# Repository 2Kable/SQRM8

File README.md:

# SQRM8

SQRM8 (say "Squaremate") is the square mate for your agents: a desk companion for
[Claude Code](https://claude.com/claude-code). A square 4" touch screen on your USB port shows every Claude Code
agent running on your machine: which one is working, which one **needs you**, what each agent and subagent is
doing, and how much of your plan is left. Built for people who run several agents in parallel and want to stop
alt-tabbing to check on them.

Nothing leaves your machine: a small daemon reads Claude Code's local data and talks to the device over the USB
cable. There is no cloud and no account. The only network access is a once-a-day look at this repository's
[Releases page](https://github.com/d-weber/SQRM8/releases) for a newer app version (public release
metadata, nothing about you); turn it off with **Check for updates daily** in the menu.

## What you see

Swipe between screens. Tap a session to open its detail view.

- **Home** is M8's Studio, a pixel-art room. M8, an original character, walks to the station of whatever your
  agents are doing: desk to write code, bookshelf to read, server rack to run commands, whiteboard to plan, bed
  when nothing runs. Subagents show up as little helpers. When a session needs you, M8 stands at the door with a
  big "!". The band below is pixel art too: clock, date and the 5-hour / weekly plan gauges, plus the per-model
  week (FA for Fable).
- **Agents** is one card per session: status, current tool, todo progress, context use, subagents.
- **Detail** shows the selected session's current action, tokens, cost, context, model and todos, with a
  **Focus** button that brings its terminal to the front.
- **Activity** is a live feed of tool calls, prompts, errors and finished turns, filterable to "needs me".
- **Usage** shows your 5-hour and weekly plan limits, today's cost and tokens, the model mix and hourly charts.
- **System** is a btop-style view of CPU, memory, top processes and network.
- **Orbit** draws sessions as planets around M8, subagents as moons.

When a session is blocked on a permission prompt or a question, an amber glow lights the edges of the screen and a
"needs you" card appears over whatever you are looking at. When a session finishes, a small celebration plays.
After a few minutes of inactivity the screen dims, then turns into a night clock.
A device that is powered up and hears nothing from the app shows a QR code to this page; once the app has talked
to it, it keeps its usual screens until the next power-up, even while the computer is off.

M8's pixel art is being redrawn; the screenshots above still show the earlier version.

## Hardware

- A Waveshare [ESP32-S3-Touch-LCD-4B](https://www.waveshare.com/wiki/ESP32-S3-Touch-LCD-4B): a 4" 480×480 IPS
  panel with capacitive touch and an ESP32-S3 behind it. The older ESP32-S3-Touch-LCD-4 (V4) was supported up to
  firmware 0.3.0 and is not any more.
- A USB-C **data** cable (not a charge-only one).

Plug the cable into the board's **USB-OTG** port, not the "USB TO UART" one. The host link runs over the
ESP32-S3's native USB, and the UART port only works for flashing. The app flashes the firmware for you.

## Install

Download the app for your OS from the [Releases page](https://github.com/d-weber/SQRM8/releases). It
bundles the device firmware, so there is nothing else to install. The builds are not code-signed, so each OS warns
once.

| OS | File | Notes |
|---|---|---|
| Windows 10/11 | `SQRM8-<ver>-windows-x64.exe` | Per-user installer, no admin rights. On the SmartScreen warning pick **More info → Run anyway**. |
| macOS (Apple silicon) | `SQRM8-<ver>-macos-arm64.dmg` | Drag the app to Applications **before** the first launch. Right-click → **Open → Open** to pass Gatekeeper (macOS 15+: open once, then System Settings → Privacy & Security → **Open Anyway**). |
| macOS (Intel) | `SQRM8-<ver>-macos-x64.dmg` | Same as above. |
| Linux | `SQRM8-<ver>-linux-x64.AppImage` | `chmod +x` and run. Needs FUSE 2 (`libfuse2`, or `libfuse2t64` on Ubuntu 24.04+). Keep the file where it is after the first run. A `.tar.gz` is available if you would rather not use an AppImage. |

Then:

1. **Start the app.** It lives in the menu bar / tray as a small M8 icon. On first start it installs its hooks
   into `~/.claude/settings.json` (after saving a backup, your own hooks and statusLine are kept) and enables
   **Start at login**. It shows one notification saying what it did.
2. **Plug in the device.** If the board is blank or runs an older firmware, the tray menu offers
   **Install firmware…** or **Update firmware…**. The board reboots and connects by itself within a minute.
3. **Start a Claude Code session.** Hooks apply to sessions started after the install, so restart any running
   ones. The screen updates in real time from there.

The tray icon's badge tells you the state at a glance: grey means no device, green connected, orange flashing
or update available, red error. The menu shows the device, your sessions and plan limits, and lets you reflash,
pick the USB port, toggle start at login or open the log.

**Updates.** When a newer app is on the Releases page the badge turns orange and the menu offers **Update app to
X…**: it downloads the build for your OS, installs it the way you installed it (new AppImage next to the old one,
the Windows installer silently, the .app replaced in Applications) and restarts. **Check for app updates…** asks
right away; `sqrm8 update` does the same from a terminal (`update --install` installs).

**Several ESP32 boards on your USB?** The app asks each ESP32-S3 port for a hello and uses the one that answers
as SQRM8. A board that does not answer (blank, or running another project) is never picked by itself:
choose it under **Device port** in the menu (or `sqrm8 port <name>`), then **Install firmware…**.
Flashing always uses the port the app talks to.

### Linux: serial port access

Your user needs write access to the device (`/dev/ttyACM0`). Either add yourself to the `dialout` group and log
back in:

```bash
sudo usermod -aG dialout $USER
```

or install the udev rule from this repo, which also stops ModemManager from grabbing the board:

```bash
sudo curl -fsSLo /etc/udev/rules.d/99-sqrm8.rules \
  https://raw.githubusercontent.com/d-weber/SQRM8/main/tools/udev/99-sqrm8.rules
sudo udevadm control --reload && sudo udevadm trigger
```

GNOME needs the AppIndicator extension to show the tray icon. KDE, Xfce, Cinnamon and most other panels show it as is.

## Plan limits

The 5-hour and weekly plan gauges need a claude.ai Pro or Max login. Claude Code only reports them to its status
line, so the app installs a tiny statusLine wrapper that records them and then runs your own statusLine command,
if you had one. They appear after the first reply in a session.

Per-model weekly limits (the "Fable" week, for instance) never reach the status line, so the daemon also asks the
claude.ai usage endpoint that Claude Code's own `/usage` dialog calls, once every 15 minutes, with the login token
Claude Code keeps in `~/.claude/.credentials.json` (the Keychain on macOS). That row shows up under 5H and 7D on
the home screen. The token is read, never stored or refreshed; to turn this off, put `{"usage_endpoint": false}`
in `~/.sqrm8/settings.json` and the row falls back to the snapshot Claude Code caches when you open
`/usage` (shown dimmed once it is more than 12 hours old).

## Uninstall

| OS | |
|---|---|
| Windows | Settings → Apps → **SQRM8** → Uninstall. Removes the hooks, the start-at-login entry and the program. |
| macOS | Quit from the menu bar, then run `"/Applications/SQRM8.app/Contents/MacOS/sqrm8" hooks uninstall` and `… autostart disable`, and move the app to the Trash. |
| Linux | Quit from the tray, then run `<AppImage> hooks uninstall` and `<AppImage> autostart disable`, and delete the file. |

Leftover state is in `~/.sqrm8` and the log folder (`~/Library/Logs`, `~/.local/state/sqrm8` or
`%LOCALAPPDATA%\sqrm8`); delete it by hand if you want a clean slate.

## If something does not work

- **Screen says "waiting for host"**: open the tray menu. It says whether the daemon sees the device, and if the
  board is on the wrong USB port.
- **No real-time updates**: restart your Claude Code sessions. If you moved the app or the AppImage, pick
  **Install Claude Code hooks** in the menu again, because the hook command contains the app's path.
- **Plan limits stay unknown**: see Plan limits above.
- **Focus does nothing in VS Code**: on macOS give the app Accessibility permission in System Settings →
  Privacy & Security.

The full troubleshooting table, the command line, the headless install for a source checkout and the internals
are in [docs/DEVELOPMENT.md](docs/DEVELOPMENT.md). The wire protocol is in [PROTOCOL.md](PROTOCOL.md).

## Privacy

Your `~/.claude` data is only read, never modified, except for the hook and statusLine entries merged into
`settings.json` at install time. The only destinations for that data are the device at the end of your USB cable
and, for the plan-limit poll described above, Anthropic's own usage endpoint (your login token goes nowhere else;
see "Plan limits" to turn that poll off).

---

This project was designed and built by a team of Claude Code agents working in parallel.
[docs/TEAM.md](docs/TEAM.md) records how.

SQRM8 is an independent product, not made, sold or endorsed by Anthropic, OpenAI or any other agent vendor.
"Claude Code" and the other product names are trademarks of their owners, used here only to say what the device
works with.

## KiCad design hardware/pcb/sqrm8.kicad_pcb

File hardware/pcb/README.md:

# sqrm8: the SQRM8 display board (KiCad 10, script-generated)

What the board is: `../BOARD.md`.
Nothing here is opened or edited in the KiCad GUI: the scripts are the sources, the KiCad files are regenerated.

The generator tools (schgen/pcbgen/router/DRC wrappers, `board.sh`) are a private toolchain, used **in place and
read-only**; the committed KiCad files open in KiCad 10 without it:
- `KICAD_TOOLS` points at the tools directory (default: a sibling checkout, see `build_sch.py`);
- `PYTHONDONTWRITEBYTECODE=1` always, so importing `schgen`/`pcbgen` leaves no `__pycache__` in the excalibur repo;
- kicad-cli is the Flatpak one and only writes under `$HOME`: outputs go to the repo or `~/.cache/kicad-tools/sqrm8/`.

## Regenerate

```bash
export KICAD_TOOLS=<tools dir> PYTHONDONTWRITEBYTECODE=1
B=$(pwd)/hardware/pcb

# schematic: build_sch.py -> sqrm8.kicad_sch / sqrm8.kicad_sym / sym-lib-table, ERC (fails on any error or warning), netlist sqrm8.net
cd "$KICAD_TOOLS/../.." && tools/kicad/board.sh "$B" sch

# PDF of the sheet and a PNG preview (outside the repo)
"$KICAD_TOOLS/kc" sch export pdf -o ~/.cache/kicad-tools/sqrm8/sqrm8.pdf "$B/sqrm8.kicad_sch"
pdftoppm -r 80 -f 1 -l 1 -singlefile -png ~/.cache/kicad-tools/sqrm8/sqrm8.pdf ~/.cache/kicad-tools/sqrm8/sqrm8_sch

# board: build_pcb.py placement + zones (reuses routes.json), then the routes from routes_manual.py + the router
cd "$KICAD_TOOLS/../.." && tools/kicad/board.sh "$B" pcb
cd "$KICAD_TOOLS/../.." && tools/kicad/board.sh "$B" route --reset   # --reset reproduces the committed board; a cached re-route adds one more GND stitching via
cd "$KICAD_TOOLS/../.." && tools/kicad/board.sh "$B" check     # DRC + silk + USB pair + mech_check.py, exit 1 on any issue
cd "$KICAD_TOOLS/../.." && tools/kicad/board.sh "$B" render    # ~/.cache/kicad-tools/sqrm8/render/
```

`build_sch.py` prints `{'symbols', 'lib_symbols', 'single_use_labels'}` and exits non-zero if a net label is used only
once (a typo). ERC needs `sqrm8.pretty/` (footprint links are checked: without the library every symbol warns).
Order after a change: `sch` -> `route` (or `pcb` when only placement or silk changed) -> `check` -> `render`.
Revision P3 passes `check` with 0 violations, 0 unconnected, 0 parity. The fab set (`fab`) and its rotation table are
kept out of the repo (`work/`, gitignored).
P3 = P2 renamed sqrm8 and relabelled; the P3 design changes (rotate C4 away from the V-cut, draw the J1 pegs as plated
Ø0.80) are still to do.

## Files

| File | Role |
|---|---|
| `build_sch.py` | the circuit: stock symbols + two drawn here (AP3032KTR-G1, the 40-pin panel FPC with the ER-TFT040-3 pin names) |
| `sqrm8.kicad_sch`, `sqrm8.kicad_sym`, `sym-lib-table`, `sqrm8.net` | generated by `board.sh ... sch` |
| `build_lib.py`, `sqrm8.pretty/` | the footprints (stock copies + drawn ones) |
| `sqrm8.kicad_pro` | design rules (: clearance/track 0.15, via 0.45/0.3, copper-edge 1.0: the V-cut margin, it also keeps the pours 1 mm in) |
| `template.kicad_pcb` | board header only: 4 layers, 1.6 mm (JLC04161H-3313: 0.0994 prepreg, 1.265 core, 1 oz outer / 0.5 oz inner), black mask, ENIG. `aux_axis_origin` (fab origin = the board's lower-left corner) is still `0 0`: set it with the outline |
| `fp-lib-table` | `sqrm8` -> `${KIPRJMOD}/sqrm8.pretty` |
| `board.env` | `RENDER_ZOOM`, `MECH_CHECK` for `board.sh` |
| `build_pcb.py` | placement (`P`), board outline, zones (In1 GND, In2 +3V3 with a VBUS island, F/B GND pours), silk, antenna keep-out |
| `routes_manual.py` | every track and via, generated from lane tables (the J2 bus, B1-B5 under the module, USB pair, power) |
| `route_board.py`, `routes.json`, `dump.json` | the router driver (only adds GND stitching vias on P2), its saved routes, the board geometry it reads |
| `sqrm8.kicad_pcb` | generated by `board.sh ... route` |
| `mech_check.py` | courtyard overlap / board-edge checker on `build_pcb.P` |
| `panel_view.py` | the board drawn on the back of the panel (`panel_view.png`) and the stack section (`panel_section.png`), stdlib + PIL, from `sqrm8.kicad_pcb` |

## Schematic conventions

- One flat A3 sheet; every pin gets a stub and a global label or power symbol (no wires between symbols).
- Nets in capitals as in `BOARD.md`; the 3.3 V rail is `+3V3` (KiCad power symbol), the 5 V input `VBUS`.
- Footprints are `sqrm8:<name>`; every BOM part carries its LCSC code (`LCSC` field) and, for ICs/connectors, `MPN`.
- Pad names the symbols expect: USB-C shell `SH` (stock symbol), panel FPC anchor pads `S1`.

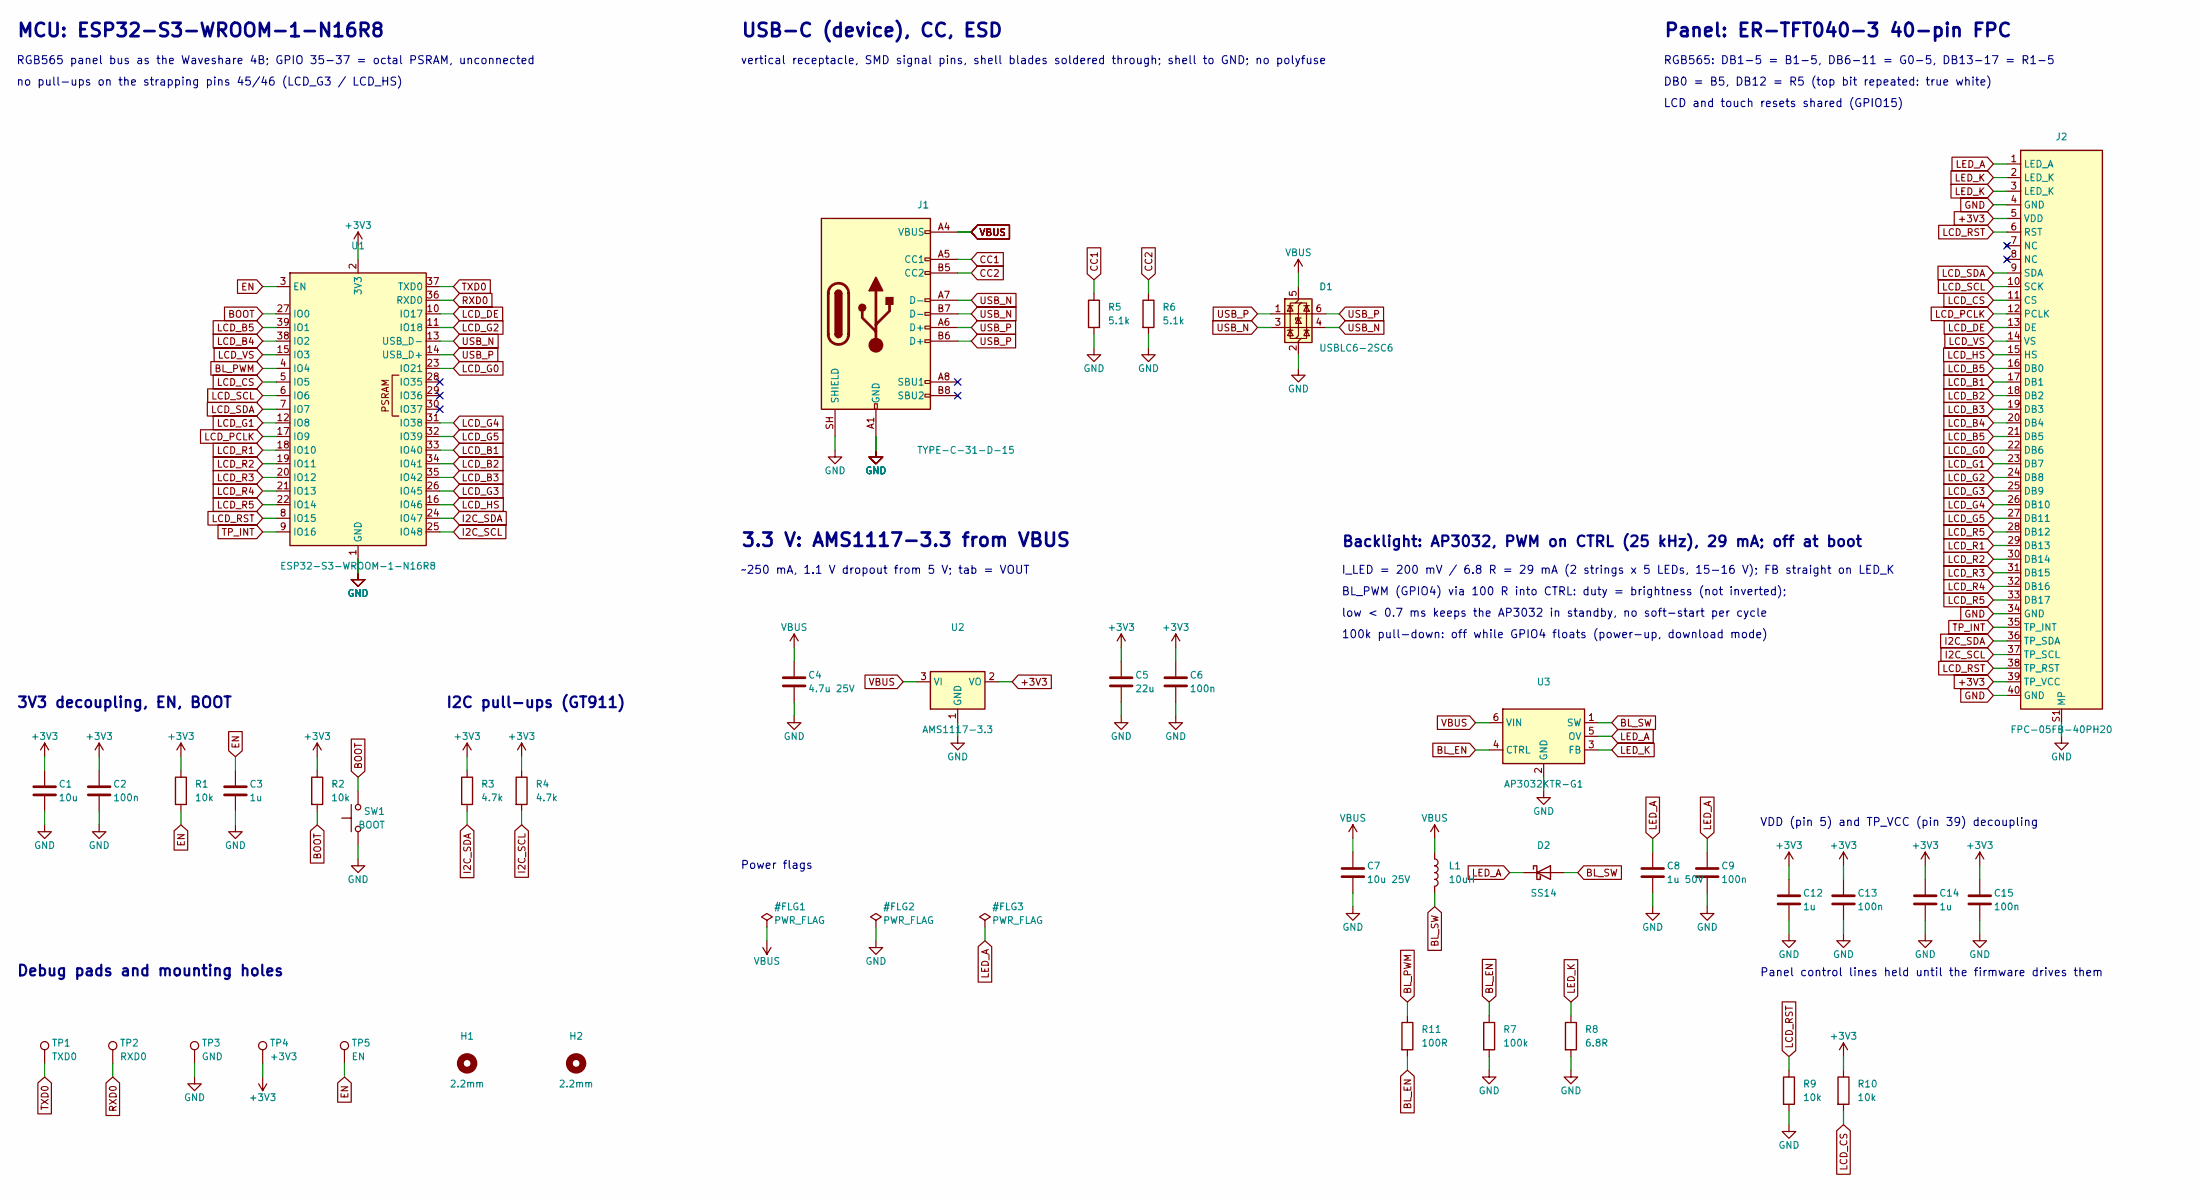
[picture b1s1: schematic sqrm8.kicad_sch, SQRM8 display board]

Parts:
C1: 10u; C_0603_1608Metric; LCSC C19702
C2, C6, C9, C13, C15: 100n; C_0603_1608Metric; LCSC C14663
C3, C12, C14: 1u; C_0603_1608Metric; LCSC C15849
C4: 4.7u 25V; C_0805_2012Metric; LCSC C1779
C5: 22u; C_0805_2012Metric; LCSC C45783
C7: 10u 25V; C_0805_2012Metric; LCSC C15850
C8: 1u 50V; C_0805_2012Metric; LCSC C28323
D1: USBLC6-2SC6; SOT-23-6; MPN USBLC6-2SC6; LCSC C2687116
D2: SS14; D_SMA; MPN SS14; LCSC C2480
H1, H2: 2.2mm; MountingHole_2.2mm
J1: TYPE-C-31-D-15; USB_C_Vertical_HRO_TYPE-C-31-D-15; MPN TYPE-C-31-D-15; LCSC C22464480
J2: FPC-05FB-40PH20; FPC_0.5mm_40P_XUNPU_FPC-05FB-40PH20; MPN FPC-05FB-40PH20; LCSC C2856837
L1: 10uH; L_SWPA3015S; MPN SWPA3015S100MT; LCSC C45403
R1, R2, R9, R10: 10k; R_0603_1608Metric; LCSC C25804
R3, R4: 4.7k; R_0603_1608Metric; LCSC C23162
R5, R6: 5.1k; R_0603_1608Metric; LCSC C23186
R7: 100k; R_0603_1608Metric; LCSC C25803
R8: 6.8R; R_0603_1608Metric; LCSC C23214
R11: 100R; R_0603_1608Metric; LCSC C22775
SW1: BOOT; SW_TS-1088; MPN TS-1088-AR02016; LCSC C720477
TP1: TXD0; TestPoint_Pad_1.5x1.5mm
TP2: RXD0; TestPoint_Pad_1.5x1.5mm
TP3: GND; TestPoint_Pad_1.5x1.5mm
TP4: +3V3; TestPoint_Pad_1.5x1.5mm
TP5: EN; TestPoint_Pad_1.5x1.5mm
U1: ESP32-S3-WROOM-1-N16R8; ESP32-S3-WROOM-1; MPN ESP32-S3-WROOM-1-N16R8; LCSC C2913202
U2: AMS1117-3.3; SOT-223-3_TabPin2; MPN AMS1117-3.3; LCSC C6186
U3: AP3032KTR-G1; SOT-23-6; MPN AP3032KTR-G1; LCSC C264086

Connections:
+3V3: C1.1, C2.1, C5.1, C6.1, C12.1, C13.1, C14.1, C15.1, J2.5 (VDD), J2.39 (TP_VCC), R1.1, R2.1, R3.1, R4.1, R10.1, TP4.1, U1.2 (3V3), U2.2 (VO)
BL_EN: R7.1, R11.2, U3.4 (CTRL)
BL_PWM: R11.1, U1.4 (IO4)
BL_SW: D2.2 (A), L1.2, U3.1 (SW)
BOOT: R2.2, SW1.2, U1.27 (IO0)
CC1: J1.A5 (CC1), R5.1
CC2: J1.B5 (CC2), R6.1
EN: C3.1, R1.2, TP5.1, U1.3 (EN)
GND: C1.2, C2.2, C3.2, C4.2, C5.2, C6.2, C7.2, C8.2, C9.2, C12.2, C13.2, C14.2, C15.2, D1.2 (GND), J1.A1 (GND), J1.A12 (GND), J1.B1 (GND), J1.B12 (GND), J1.SH (SHIELD), J2.4 (GND), J2.34 (GND), J2.40 (GND), J2.S1 (MP), R5.2, R6.2, R7.2, R8.2, R9.2, SW1.1, TP3.1, U1.1 (GND), U1.40 (GND), U1.41 (GND), U2.1 (GND), U3.2 (GND)
I2C_SCL: J2.37 (TP_SCL), R4.2, U1.25 (IO48)
I2C_SDA: J2.36 (TP_SDA), R3.2, U1.24 (IO47)
LCD_B1: J2.17 (DB1), U1.33 (IO40)
LCD_B2: J2.18 (DB2), U1.34 (IO41)
LCD_B3: J2.19 (DB3), U1.35 (IO42)
LCD_B4: J2.20 (DB4), U1.38 (IO2)
LCD_B5: J2.16 (DB0), J2.21 (DB5), U1.39 (IO1)
LCD_CS: J2.11 (CS), R10.2, U1.5 (IO5)
LCD_DE: J2.13 (DE), U1.10 (IO17)
LCD_G0: J2.22 (DB6), U1.23 (IO21)
LCD_G1: J2.23 (DB7), U1.12 (IO8)
LCD_G2: J2.24 (DB8), U1.11 (IO18)
LCD_G3: J2.25 (DB9), U1.26 (IO45)
LCD_G4: J2.26 (DB10), U1.31 (IO38)
LCD_G5: J2.27 (DB11), U1.32 (IO39)
LCD_HS: J2.15 (HS), U1.16 (IO46)
LCD_PCLK: J2.12 (PCLK), U1.17 (IO9)
LCD_R1: J2.29 (DB13), U1.18 (IO10)
LCD_R2: J2.30 (DB14), U1.19 (IO11)
LCD_R3: J2.31 (DB15), U1.20 (IO12)
LCD_R4: J2.32 (DB16), U1.21 (IO13)
LCD_R5: J2.28 (DB12), J2.33 (DB17), U1.22 (IO14)
LCD_RST: J2.6 (RST), J2.38 (TP_RST), R9.1, U1.8 (IO15)
LCD_SCL: J2.10 (SCK), U1.6 (IO6)
LCD_SDA: J2.9 (SDA), U1.7 (IO7)
LCD_VS: J2.14 (VS), U1.15 (IO3)
LED_A: C8.1, C9.1, D2.1 (K), J2.1 (LED_A), U3.5 (OV)
LED_K: J2.2 (LED_K), J2.3 (LED_K), R8.1, U3.3 (FB)
RXD0: TP2.1, U1.36 (RXD0)
TP_INT: J2.35 (TP_INT), U1.9 (IO16)
TXD0: TP1.1, U1.37 (TXD0)
USB_N: D1.3 (I/O2), D1.4 (I/O2), J1.A7 (D-), J1.B7 (D-), U1.13 (USB_D-)
USB_P: D1.1 (I/O1), D1.6 (I/O1), J1.A6 (D+), J1.B6 (D+), U1.14 (USB_D+)
VBUS: C4.1, C7.1, D1.5 (VBUS), J1.A4 (VBUS), J1.A9 (VBUS), J1.B4 (VBUS), J1.B9 (VBUS), L1.1, U2.3 (VI), U3.6 (VIN)

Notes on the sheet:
MCU: ESP32-S3-WROOM-1-N16R8
RGB565 panel bus as the Waveshare 4B; GPIO 35-37 = octal PSRAM, unconnected
no pull-ups on the strapping pins 45/46 (LCD_G3 / LCD_HS)
3V3 decoupling, EN, BOOT
I2C pull-ups (GT911)
Debug pads and mounting holes
USB-C (device), CC, ESD
vertical receptacle, SMD signal pins, shell blades soldered through; shell to GND; no polyfuse
3.3 V: AMS1117-3.3 from VBUS
~250 mA, 1.1 V dropout from 5 V; tab = VOUT
Power flags
Backlight: AP3032, PWM on CTRL (25 kHz), 29 mA; off at boot
I_LED = 200 mV / 6.8 R = 29 mA (2 strings x 5 LEDs, 15-16 V); FB straight on LED_K
BL_PWM (GPIO4) via 100 R into CTRL: duty = brightness (not inverted);
low < 0.7 ms keeps the AP3032 in standby, no soft-start per cycle
100k pull-down: off while GPIO4 floats (power-up, download mode)
Panel: ER-TFT040-3 40-pin FPC
RGB565: DB1-5 = B1-5, DB6-11 = G0-5, DB13-17 = R1-5
DB0 = B5, DB12 = R5 (top bit repeated: true white)
LCD and touch resets shared (GPIO15)
VDD (pin 5) and TP_VCC (pin 39) decoupling
Panel control lines held until the firmware drives them

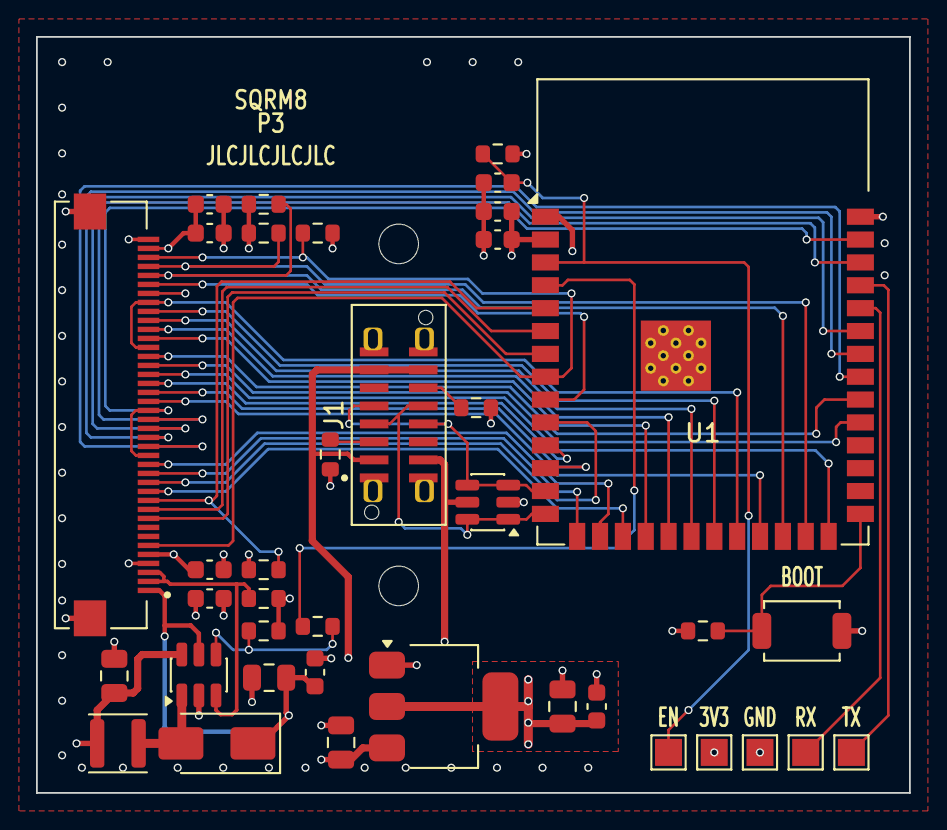
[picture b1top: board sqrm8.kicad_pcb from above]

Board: 4 copper layers, 48.5 x 42.0 mm, 40 parts (0 on the bottom side), 43 nets.

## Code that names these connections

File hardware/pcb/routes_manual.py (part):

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
Structure:
  * J2 (panel FPC): every bus pin drops to B.Cu through a via in one of three columns (pin number mod 3, 0.95 mm apart, so the
    antipads on In1/In2 do not merge into a slot). LCD_CS/SCL/SDA and the first LCD_RST pin stay on F.Cu (the "init fan").
  * Init fan (F.Cu): J2 pins 11/10/9/6 north along x 10-10.9, east over J1's top (between H1 and J1's peg), down into U1
    pins 5-8 from the west. LCD_CS reaches its pull-up R10 by a short B.Cu hop under the fan.
  * B.Cu ribbon, in J2 order: the north group (LCD_RST from pin 38, I2C_SCL, I2C_SDA, TP_INT) across J1's top; the south block
    (R5-R1, G5-G0, HS, VS, DE, PCLK) under J1 between its shell pads, then fanned to 0.46 mm in the channel and run under the
    module, each line ending in a via with a short F.Cu stub to its pad (bottom row from above, left/right column sideways).
  * B1-B5 (J2 pins 17-21) go west under J2, north along the edge, east along the top band and under the module's top edge,
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  * USB: P joins A6-B6 by a diagonal in J1's row gap and leaves down the gap, hops under J1's bottom on B.Cu and enters D1
    pin 6 from below; N joins A7-B7 by a B.Cu crossover and enters D1 pin 4 from above; D1's pins 4-3 and 6-1 are linked
    under its body (KiCad has no internal link), pins 3/1 go on to U1 pins 13/14. VBUS reaches D1 pin 5 from the west.
  * EN and BL_PWM leave U1 pins 3/4 eastwards on F.Cu under the module (the only free side), cross the bottom row on B.Cu
    through gaps between the stubs, and run to TP5 / R11 on B.Cu below the module.
"""
import build_pcb as bp
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for net, n, yj, ym, xd in NORTH:
    q = drop(net, n)
    NEND[net] = [q, (XN, q[1]), (XN + (yj - q[1]), yj), (xd, yj), (xd + (ym - yj), ym)]
# LCD_RST (pin 38): via left of U1 pin 8, F.Cu down into the pad (east side; the init fan's RST enters from the west)
RSTV = (29.7, 14.25)
t('LCD_RST', B, SIG, *NEND['LCD_RST'], RSTV); v('LCD_RST', *RSTV)
e = u1(8); t('LCD_RST', F, SIG, RSTV, (RSTV[0], e[1] - 0.48), (RSTV[0] - 0.48, e[1]), e)
# I2C: under the module above the exposed pad, to vias over their bottom-row pads, F.Cu straight down
# (I2C_SDA's via drops 0.45 below its lane: I2C_SCL runs on past it to pin 25)
for net, pin, dy in (('I2C_SCL', 25, 0.0), ('I2C_SDA', 24, 0.45)):
    e = u1(pin); a = NEND[net][-1]; q = (e[0], a[1] + dy)
    t(net, B, SIG, *NEND[net], (q[0] - dy, a[1]), q); v(net, *q); t(net, F, SIG, q, e)
# TP_INT: drops 0.2 to its via so that I2C_SDA keeps 0.5 mm, F.Cu down east of the RST stub into pin 9
TPV = (30.4, 15.55); a = NEND['TP_INT'][-1]
t('TP_INT', B, SIG, *NEND['TP_INT'], (TPV[0] - (TPV[1] - a[1]), a[1]), TPV); v('TP_INT', *TPV)
e = u1(9); t('TP_INT', F, SIG, TPV, (TPV[0], e[1] - 0.55), (TPV[0] - 0.55, e[1]), e)

# south block: (net, J2 pin), in J2 order; J1 y: 11 lanes north of the USB_N crossover, 4 south of it
SOUTH = [('LCD_R5', 33), ('LCD_R4', 32), ('LCD_R3', 31), ('LCD_R2', 30), ('LCD_R1', 29), ('LCD_G5', 27), ('LCD_G4', 26),
         ('LCD_G3', 25), ('LCD_G2', 24), ('LCD_G1', 23), ('LCD_G0', 22), ('LCD_HS', 15), ('LCD_VS', 14), ('LCD_DE', 13),
         ('LCD_PCLK', 12)]
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def bottom(net, pin):
    """Lane to a via above its bottom-row pad, F.Cu stub straight down."""
    e = u1(pin); q = (e[0], SEND[net][-1][1]); t(net, B, SIG, *SEND[net], q); v(net, *q); t(net, F, SIG, q, e)
for net, pin in (('LCD_R5', 22), ('LCD_R4', 21), ('LCD_R3', 20), ('LCD_R2', 19), ('LCD_R1', 18), ('LCD_G0', 23),
                 ('LCD_VS', 15), ('LCD_PCLK', 17)):
    bottom(net, pin)
# lane-end vias are kept >= 1.13 mm apart so their In1/In2 antipads (0.85) never merge into a slot under the bus
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JA4, JA5, JA6, JA7, JA9 = (p('J1', n) for n in ('A4', 'A5', 'A6', 'A7', 'A9'))
JB4, JB5, JB6, JB7, JB9 = (p('J1', n) for n in ('B4', 'B5', 'B6', 'B7', 'B9'))
DP1, DG2, DN3, DN4, DV5, DP6 = (p('D1', str(i)) for i in range(1, 7))
# USB_P: A6-B6 diagonal in the row gap, down the gap, B.Cu under J1's bottom, up into D1 pin 6, link 6-1, on to U1 pin 14
PX = 20.1
t('USB_P', F, HS, JA6, (PX - 0.5, JA6[1]), (PX + 0.5, JB6[1]), JB6)
PV1, PV2 = (PX, 26.95), (DP6[0], 27.6625)
t('USB_P', F, HS, (PX, JA6[1] - 0.5), PV1); v('USB_P', *PV1)
t('USB_P', B, HS, PV1, (PX + 0.35, 27.3), (PV2[0] - 0.3625, 27.3), PV2); v('USB_P', *PV2)
t('USB_P', F, HS, PV2, DP6, DP1, (27.2, DP1[1]), (27.2 + (DP1[1] - u1(14)[1]), u1(14)[1]), u1(14))
# USB_N: A7 west to a via, B.Cu crossover under J1, via east of B7, down into D1 pin 4, link 4-3, on to U1 pin 13
NV1, NV2 = (17.35, JA6[1]), (22.85, JB7[1])
t('USB_N', F, HS, JA7, (NV1[0] + 0.25, JA7[1]), (NV1[0], JA7[1] + 0.25), NV1); v('USB_N', *NV1)
t('USB_N', B, HS, NV1, NV2); v('USB_N', *NV2)
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t('VBUS', F, 0.4, JB9, (VX, JB9[1]), (VX, 33.6)); v('VBUS', VX, 33.6)
t('VBUS', F, 0.3, (VX, DV5[1]), DV5)

# ================================================================== U1 supply, EN, BL_PWM, GND pins
C1V, C2V, C3E, R1E, R1V = p('C1', '1'), p('C2', '1'), p('C3', '1'), p('R1', '2'), p('R1', '1')
t('+3V3', F, PWR, u1(2), C2V, C1V); t('+3V3', F, PWR, C2V, (C2V[0], 12.15)); v('+3V3', C2V[0], 12.15)
t('GND', F, 0.25, p('C3', '2'), p('C1', '2'), p('C2', '2'), (p('C2', '2')[0], 12.15)); v('GND', p('C2', '2')[0], 12.15)
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t('EN', F, SIG, u1(3), (ENX, u1(3)[1]), ENV3); v('EN', *ENV3)
t('EN', B, SIG, ENV3, (ENX, ENV4[1] - (ENX - ENV4[0])), ENV4); v('EN', *ENV4)
t('EN', F, SIG, ENV4, (TP5[0], ENV4[1] + (ENV4[0] - TP5[0])), TP5)
# BL_PWM: pin 4 east under the module, down through the PCLK/R1 gap, B.Cu west under J1's bottom (north of H2), F.Cu to R11
BPX, R11P = 33.19, p('R11', '1')
BPV1, BPV2 = (BPX, 25.2), (14.6, 28.4)                 # BPV1 1.18 mm from PCLK's via: separate antipads
t('BL_PWM', F, SIG, u1(4), (29.2, u1(4)[1]), (29.5, u1(4)[1] - 0.3), (BPX, u1(4)[1] - 0.3), BPV1); v('BL_PWM', *BPV1)
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t('VBUS', F, 0.4, L1V, (L1V[0], 37.4), (C7V[0], C7V[1]), (5.6, C7V[1]), (5.6, U3[6][1]), U3[6])
for pad_, via in ((U3[2], (U3[2][0], 37.7)), (C8G, (C8G[0], 36.95)), (C7G, (C7G[0], 33.6)), (C9G, (16.35, C9G[1]))):
    t('GND', F, PWR, pad_, via); v('GND', *via)
# LED_K: J2 pins 2/3 between C13 and C12, R8 (sense), down west of R7/C8 into U3 FB from below
k2, k3, R8K = j2(2), j2(3), p('R8', '1')
KX, KY = 11.1, 30.4
t('LED_K', F, 0.2, k3, (7.05, k3[1]), (7.05, k2[1]))
t('LED_K', F, 0.2, k2, (7.25, k2[1]), (7.4, KY), (KX, KY))                 # split at the R8 branch: a real junction
t('LED_K', F, 0.2, (KX, KY), (KX, 37.65), (U3[3][0], 37.65), U3[3])
t('LED_K', F, 0.2, (KX, KY), (R8K[0], KY), R8K)
# LED_A: J2 pin 1 -> U3 OV from above; B.Cu hop under U3 / D2 to D2's cathode, C8 and C9
a1 = j2(1); LAX = 7.1; LAV1, LAV2 = (LAX, 33.3), (14.0, 37.7)
t('LED_A', F, 0.25, a1, (a1[0] + 0.6, a1[1]), (LAX, a1[1] + 0.3), LAV1); v('LED_A', *LAV1)
t('LED_A', F, 0.25, (LAX, 32.7), (8.55, 32.7), (U3[5][0], 33.15), U3[5])
t('LED_A', B, 0.25, LAV1, (LAX, 38.6), (13.1, 38.6), LAV2); v('LED_A', *LAV2)
t('LED_A', F, 0.3, LAV2, (C8A[0], LAV2[1] - 0.15), C8A, (14.85, C8A[1]), (C9A[0] - 0.125, C9A[1]), C9A)
t('LED_A', F, 0.3, LAV2, (13.4, 38.3), (D2K[0] + 0.45, D2K[1]), D2K)
# BL_EN (CTRL): U3 pin 4 -> B.Cu east under R7 / C8 -> R7 (pull-down) and R11 (series from BL_PWM)
R7E, R11E = p('R7', '1'), p('R11', '2')
EV1, EV2, EV3 = (U3[4][0], 33.1), (R7E[0], 34.05), (R11E[0], 33.725)
t('BL_EN', F, SIG, U3[4], EV1); v('BL_EN', *EV1)
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
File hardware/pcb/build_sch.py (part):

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# ---------------------------------------------------------------- MCU: ESP32-S3-WROOM-1-N16R8 (pin map = firmware/src/core/board.h)
g.text('MCU: ESP32-S3-WROOM-1-N16R8', (15, 25), 2.5, True)
g.text('RGB565 panel bus as the Waveshare 4B; GPIO 35-37 = octal PSRAM, unconnected', (15, 30), 1.5)
g.text('no pull-ups on the strapping pins 45/46 (LCD_G3 / LCD_HS)', (15, 34), 1.5)
GPIO = {0: 'BOOT', 1: 'LCD_B5', 2: 'LCD_B4', 3: 'LCD_VS', 4: 'BL_PWM', 5: 'LCD_CS', 6: 'LCD_SCL', 7: 'LCD_SDA', 8: 'LCD_G1',
        9: 'LCD_PCLK', 10: 'LCD_R1', 11: 'LCD_R2', 12: 'LCD_R3', 13: 'LCD_R4', 14: 'LCD_R5', 15: 'LCD_RST', 16: 'TP_INT',
        17: 'LCD_DE', 18: 'LCD_G2', 21: 'LCD_G0', 35: 'NC', 36: 'NC', 37: 'NC', 38: 'LCD_G4', 39: 'LCD_G5', 40: 'LCD_B1',
        41: 'LCD_B2', 42: 'LCD_B3', 45: 'LCD_G3', 46: 'LCD_HS', 47: 'I2C_SDA', 48: 'I2C_SCL'}
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R('R5', '5.1k', (215, 75), 'CC1', 'GND', desc='CC1 Rd pull-down (UFP, 5 V default power)')
R('R6', '5.1k', (225, 75), 'CC2', 'GND', desc='CC2 Rd pull-down (UFP, 5 V default power)')
g.add('D1', 'Power_Protection:USBLC6-2SC6', grid(255, 75), 0, value='USBLC6-2SC6', footprint='sqrm8:SOT-23-6', lcsc='C2687116',
      mpn='USBLC6-2SC6', desc='ESD on D+/D- and VBUS at J1', pins={'1': 'USB_P', '6': 'USB_P', '3': 'USB_N', '4': 'USB_N', '2': 'GND', '5': 'VBUS'})

g.text('3.3 V: AMS1117-3.3 from VBUS', (150, 120), 2.5, True)
g.text('~250 mA, 1.1 V dropout from 5 V; tab = VOUT', (150, 125), 1.5)
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# ---------------------------------------------------------------- backlight: AP3032 boost, Waveshare 4B topology, VIN from VBUS
g.text('Backlight: AP3032, PWM on CTRL (25 kHz), 29 mA; off at boot', (262, 120), 2.0, True)
g.text('I_LED = 200 mV / 6.8 R = 29 mA (2 strings x 5 LEDs, 15-16 V); FB straight on LED_K', (262, 125), 1.5)
g.text('BL_PWM (GPIO4) via 100 R into CTRL: duty = brightness (not inverted);', (262, 129), 1.5)
g.text('low < 0.7 ms keeps the AP3032 in standby, no soft-start per cycle', (262, 133), 1.5)
g.text('100k pull-down: off while GPIO4 floats (power-up, download mode)', (262, 137), 1.5)
g.add('U3', 'sqrm8_custom:AP3032KTR-G1', grid(300, 155), 0, value='AP3032KTR-G1', footprint='sqrm8:SOT-23-6', lcsc='C264086',
      mpn='AP3032KTR-G1', desc='WLED boost, 1 MHz, FB 200 mV, OVP 27 V',
      pins={'6': 'VBUS', '4': 'BL_EN', '1': 'BL_SW', '5': 'LED_A', '3': 'LED_K', '2': 'GND'})
C('C7', '10u 25V', (265, 180), 'VBUS', 'GND', desc='U3 VIN')
g.add('L1', 'Device:L', grid(280, 180), 0, value='10uH', footprint='sqrm8:L_SWPA3015S', lcsc='C45403', mpn='SWPA3015S100MT',
      desc='boost inductor 10 uH, 3x3x1.5 mm', pins={'1': 'VBUS', '2': 'BL_SW'})
g.add('D2', 'Diode:SS14', grid(300, 180), 0, value='SS14', footprint='sqrm8:D_SMA', lcsc='C2480', mpn='SS14',
      desc='boost rectifier, Schottky 40 V 1 A', pins={'2': 'BL_SW', '1': 'LED_A'})
C('C8', '1u 50V', (320, 180), 'LED_A', 'GND', desc='boost output (LED_A up to ~16 V, OVP 27 V)')
C('C9', '100n', (330, 180), 'LED_A', 'GND', desc='boost output HF (50 V part)')
R('R11', '100R', (275, 210), 'BL_PWM', 'BL_EN', desc='BL_PWM (GPIO4) into CTRL, 25 kHz PWM')
R('R7', '100k', (290, 210), 'BL_EN', 'GND', desc='CTRL pull-down: backlight off until GPIO4 drives it')
R('R8', '6.8R', (305, 210), 'LED_K', 'GND', desc='LED current sense 6.8 R 1 %: 29 mA')

# ---------------------------------------------------------------- panel FPC (ER-TFT040-3 pinout, datasheet p.6)
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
